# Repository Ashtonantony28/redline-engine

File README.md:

# Redline

A code-first digital twin of a 2.0 L naturally aspirated inline-4: parametric CAD (build123d),
crank-angle thermodynamics and combustion (Cantera), 1D gas dynamics, kinematics, dynamics and NVH,
structural FEA, and an engine control unit that runs hardware-in-the-loop on the Vortex-V RISC-V core.

All numbers are **modelled**. Plan: see `docs/PLAN.md`.

## Gallery

*The three.js replay (`viz/replay/index.html`) at 3000 rpm, wide-open throttle. It shows the CAD crank train moving with exact slider-crank kinematics, next to cylinder 1's P-V loop, the four cylinder pressures, crank torque and valve lift. Pressures come from the M4 1D gas-dynamics engine. **All numbers are modelled**; there is no physical engine. Recorded headless with `node viz/record_demo.mjs`. [MP4](docs/media/replay.mp4)*

| | |
|---|---|
|  |  |
|  |  |

*CAD renders from `cad/` (build123d). The interference audit is in [docs/CAD-AUDIT.md](docs/CAD-AUDIT.md).*

## Quick start
```
pip install -r requirements.txt
pytest -q
```

## Vehicle, replay and report (M10)
```
python -m vehicle.wltp                 # WLTP Class 3b L/100 km and g CO2/km (generic compact sedan, spec/vehicle.yaml)
python -m vehicle.accel                # 0-100 km/h and 80-120 km/h in gear
python -m vehicle.wot_fixture          # regenerate fixtures/wot/wot_coarse.csv from the M4 model (reviewed change)
python -m dyn.report --pressure m4     # M5 dynamics on real M4 / thermo pressure traces, vs the placeholder
python -m viz.build --check            # three.js replay viz/replay/index.html + headless check (node playwright)
python -m report.build                 # docs/REPORT.md technical report, figures under out/
pytest -q tests/test_m10_vehicle.py tests/test_m5_dynamics.py
```
The technical report is `docs/REPORT.md`; every number in it is computed by `report/build.py` and is modelled.

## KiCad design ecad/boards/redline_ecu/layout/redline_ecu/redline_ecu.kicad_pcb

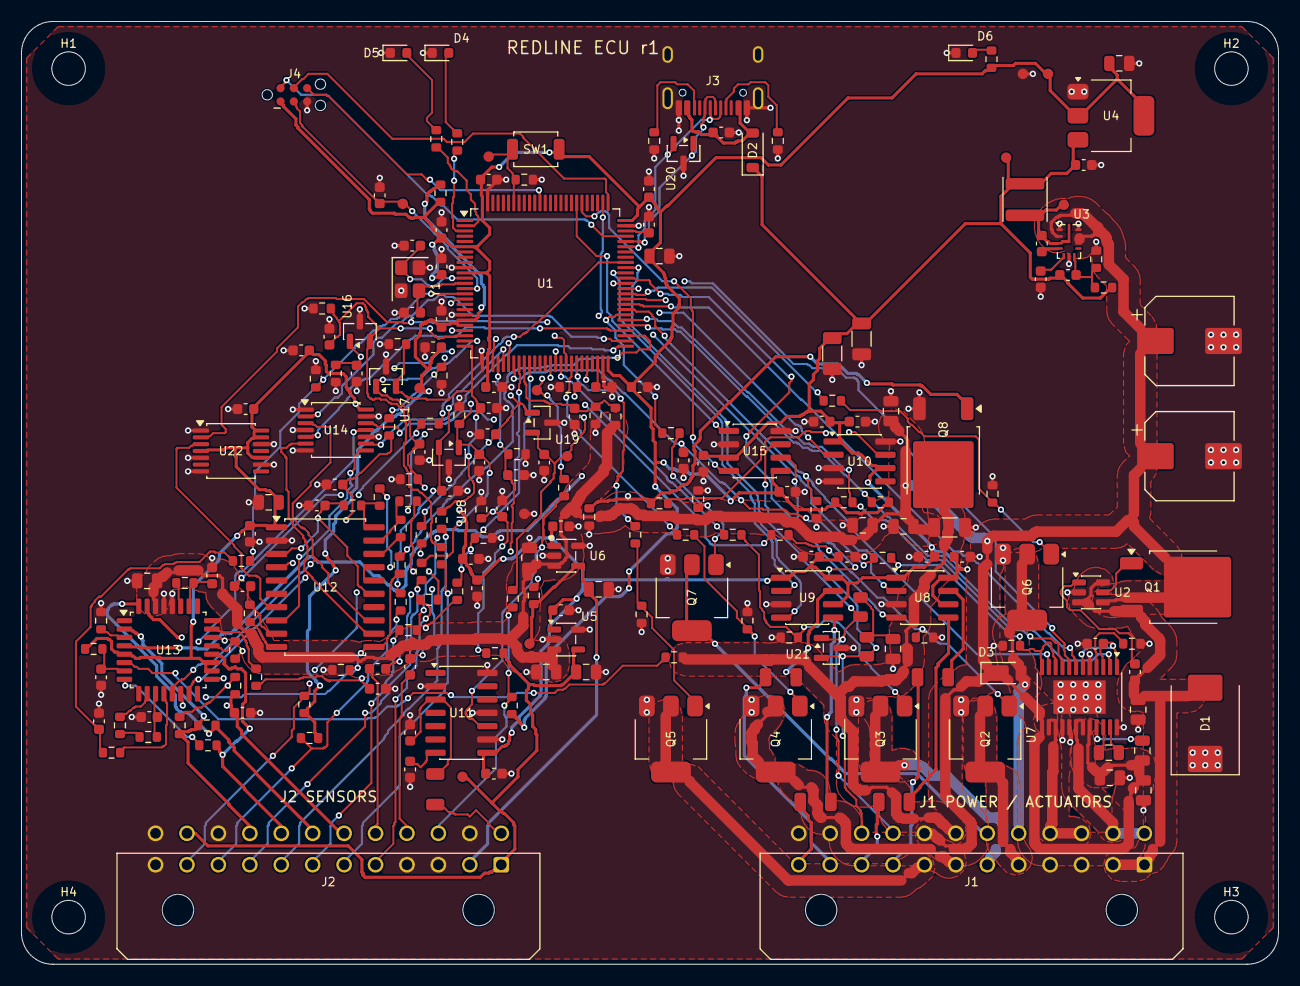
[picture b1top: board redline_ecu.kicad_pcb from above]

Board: 4 copper layers, 120.0 x 90.0 mm, 230 parts (0 on the bottom side), 158 nets.

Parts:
C1, C2: 47uF 50V; CP_Elec_8x10
C3: 4.7nF 100V X7R; C_0805_2012Metric
C4, C5, C6, C13, C14, C21, C28, C30, C31, C32, C35, C39, C40, C41, C42, C43, C44, C45, C48, C50, C53, C58, C61, C64, C68, C72, C73, C81, C83: 100nF 50V X7R; C_0603_1608Metric
C7: 47nF 100V X7R; C_0805_2012Metric
C8, C27, C38, C47, C49, C59, C69: 1uF 25V X7R; C_0603_1608Metric
C9, C74, C75, C76, C77, C78, C79, C80: 10nF 50V X7R; C_0603_1608Metric
C10, C12: 1uF 50V X7R; C_0805_2012Metric
C11, C54, C55, C62, C65, C67, C70: 100nF 100V X7R; C_0805_2012Metric
C15, C71, C82: 1nF 50V C0G; C_0603_1608Metric
C16, C19, C20: 33nF 50V X7R; C_0603_1608Metric
C17: 33nF 100V X7R; C_0805_2012Metric
C18: 220pF 50V C0G; C_0603_1608Metric
C22, C23: 3.3nF 50V C0G; C_0603_1608Metric
C24: 470pF 50V C0G; C_0603_1608Metric
C25: 2.2nF 50V C0G; C_0603_1608Metric
C26: 22nF 50V X7R; C_0603_1608Metric
C29, C63, C66: 4.7uF 16V X7R; C_0805_2012Metric
C33, C34: 12pF 50V C0G; C_0603_1608Metric
C36, C37: 2.2uF 10V X7R; C_0603_1608Metric
C46, C60: 10uF 16V X7R; C_0805_2012Metric
C51, C52: 22uF 16V X7R; C_1206_3216Metric
C56: 4.7uF 50V X7R; C_1206_3216Metric
C57: 20pF 50V C0G; C_0603_1608Metric
D1: 24V TVS Diode; D_SMC
D2: B5819W; D_SOD-123
D3: SBR3U60P1; D_PowerDI-123
D4: LED RED; LED_0603_1608Metric
D5: LED BLUE; LED_0603_1608Metric
D6: LED GREEN; LED_0603_1608Metric
FB1: 600 1A 100MHz; R_0603_1608Metric
H1, H2, H3, H4: MountingHole; MountingHole_3.2mm_M3
J1, J2: 43045-2400; Molex_Micro-Fit_3.0_43045-2400_2x12_P3.00mm_Horizontal
J3: TYPE-C-31-M-12; USB_C_Receptacle_HRO_TYPE-C-31-M-12
J4: TC2030-IDC-NL; Tag-Connect_TC2030-IDC-NL_2x03_P1.27mm_Vertical
L1: 3.3uH; L_Sunlord_SWPA4030S
Q1, Q8: DMTH6016LK3Q-13; TO-252-2
Q2, Q3, Q4, Q5, Q6, Q7: ZXMS6006DGQTA; SOT-223-3_TabPin2
R1, R2: 60.4 1%; R_0805_2012Metric
R3, R4: 5.1k 1%; R_0603_1608Metric
R5, R8, R12, R15, R17, R20, R26, R29, R34, R40, R62, R86: 10k 1%; R_0603_1608Metric
R6: 390 1%; R_0603_1608Metric
R7, R19, R25, R32, R38, R41, R42, R47, R49, R51, R53, R55, R57, R61, R64, R66, R68: 1k 1%; R_0603_1608Metric
R9, R13, R23, R39, R48, R50, R52, R54, R56, R58, R60: 100k 1%; R_0603_1608Metric
R10: 68k 1%; R_0603_1608Metric
R11, R21, R27: 6.8k 1%; R_0603_1608Metric
R14: 21.5k 1%; R_0603_1608Metric
R16: 301 1%; R_0603_1608Metric
R18: 61.9 0.1%; R_0603_1608Metric
R22: 470k 1%; R_0603_1608Metric
R24, R65: 4.7k 1%; R_0603_1608Metric
R28: 22 1%; R_0603_1608Metric
R30, R35, R36, R37, R63: 47k 1%; R_0603_1608Metric
R31: 1M 1%; R_0603_1608Metric
R33, R70, R72, R74, R76, R78, R80, R82, R84: 20k 1%; R_0603_1608Metric
R43, R44, R45, R46: 100 1%; R_1206_3216Metric
R59: 24.9k 1%; R_0603_1608Metric
R67, R69: 2.49k 1%; R_0603_1608Metric
R71, R73, R75, R77, R79, R81, R83: 13.3k 1%; R_0603_1608Metric
R85: 22k 1%; R_1206_3216Metric
SW1: TS-1088-AR02016; SW_SPST_TS-1088-xR020
TP1, TP2, TP3, TP4, TP5, TP6, TP7, TP8, TP9, TP10, TP11, TP12, TP13: TestPoint_Small; TestPoint_Pad_D1.0mm
U1: STM32H743VIT6; LQFP-100_14x14mm_P0.5mm
U2: LM74700QDBVRQ1; SOT-23-6
U3: LMR36015FSCQRNXRQ1; Texas_RNX0012C_VQFN-14-11-1EP_2x3mm_P0.5mm_EP0.25x1.825mm
U4: LDL1117S33R; SOT-223-3_TabPin2
U5, U6: TPS7B4250QDBVRQ1; SOT-23-5
U7: DRV8873HQPWPRQ1; HTSSOP-24-1EP_4.4x7.8mm_P0.65mm_EP3.2x5mm
U8, U9, U10: UCC27524AQDRQ1; SOIC-8_3.9x4.9mm_P1.27mm
U11: LM1815M/NOPB; SOIC-14_3.9x8.7mm_P1.27mm
U12: TPIC8101DWRQ1; SOIC-20W_7.5x12.8mm_P1.27mm
U13: CJ125; LQFP-32_7x7mm_P0.8mm
U14, U22: SN74AHCT125QPWRQ1; TSSOP-14_4.4x5mm_P0.65mm
U15: TCAN1044AVDRQ1; SOIC-8_3.9x4.9mm_P1.27mm
U16, U17, U18, U19, U20: TPD2E2U06QDBZRQ1; SOT-23
U21: ESD2CAN24DBZRQ1; SOT-23
Y1: 8MHz; Crystal_SMD_3225-4Pin_3.2x2.5mm

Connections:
3V3: C5.1, C40.1, C41.1, C42.1, C43.1, C44.1, C45.1, C46.1, C60.1, FB1.1, J4.1, R5.2, R8.2, R61.1, R65.2, SW1.1, TP3.1, U1.6, U1.11, U1.27, U1.50, U1.75, U1.100, U4.2, U15.5
5V: C4.1, C20.1, C21.1, C27.1, C28.1, C29.1, C30.1, C31.1, C32.1, C47.1, C48.1, C49.1, C50.1, C51.1, C52.1, C57.1, C59.1, C61.1, C64.1, C81.1, D2.1, L1.2, R17.2, R60.1, TP2.1, U4.3, U5.1, U6.1, U8.1, U8.6, U8.8, U9.1, U9.6, U9.8, U10.1, U10.6, U11.8, U12.1, U13.5, U13.18, U13.19, U14.14, U15.3, U22.4, U22.10, U22.13, U22.14
5V_S1: C63.1, J2.1, J2.23, R77.1, TP5.1, U5.4
5V_S2: C66.1, J2.2, R79.1, TP6.1, U6.4
BOOT0: R40.1, SW1.2, TP12.1, U1.94
CAM: C71.1, R64.2, TP10.1, U1.46, U19.2
CAM_IN: J2.15, R64.1, R65.1
CAN_H: J1.21, R1.1, U15.7, U21.1
CAN_L: J1.22, R2.2, U15.6, U21.2
CAN_RX: U1.81, U15.4
CAN_TX: U1.82, U15.1
CLT: J2.11, R66.1, R67.1
CLT_ADC: C72.1, R66.2, U1.31, U19.1
COM.CAN_SPLIT: C3.1, R1.2, R2.1
COM.USB_CC1: J3.A5, R3.1
COM.USB_CC2: J3.B5, R4.1
CRANK: R84.1, R86.2, TP9.1, U1.77
CRANK_P: J2.13, R85.1
ETB.CPH: C7.1, U7.22
ETB.CPL: C7.2, U7.23
ETB.DVDD: C8.1, U7.1, U7.3, U7.6
ETB.IPROPI: R6.1, R7.1, U7.10, U7.12
ETB.SR: R10.1, U7.4
ETB.VCP: C10.1, U7.21
ETB_DISABLE: R5.1, U1.56, U7.9
ETB_IN1: U1.59, U7.7
ETB_IN2: U1.60, U7.8
ETB_ISENSE: C9.1, R7.2, U1.32
ETB_M_N: J1.15, J1.16, U7.14, U7.15
ETB_M_P: J1.13, J1.14, U7.18, U7.19
ETB_NFAULT: R8.1, U1.55, U7.2
ETB_NSLEEP: R9.1, U1.58, U7.11
GND: C1.2, C2.2, C3.2, C4.2, C5.2, C6.2, C8.2, C9.2, C11.2, C12.2, C13.2, C14.2, C15.2, C16.2, C17.2, C18.2, C19.2, C20.2, C21.2, C25.2, C26.2, C27.2, C28.2, C29.2, C30.2, C31.2, C32.2, C33.2, C34.2, C35.2, C36.2, C37.2, C38.2, C39.2, C40.2, C41.2, C42.2, C43.2, C44.2, C45.2, C46.2, C47.2, C48.2, C49.2, C50.2, C51.2, C52.2, C54.2, C55.2, C56.2, C59.2, C60.2, C61.2, C62.2, C63.2, C64.2, C65.2, C66.2, C67.2, C68.2, C69.2, C70.2, C71.2, C72.2, C73.2, C74.2, C75.2, C76.2, C77.2, C78.2, C79.2, C80.2, C81.2, C82.2, C83.2, D1.1, D4.1, D5.1, D6.1, J1.3, J1.4, J1.23, J1.24, J2.3, J2.4, J2.12, J2.14, J2.22, J2.24, J3.A1, J3.A12, J3.B1, J3.B12, J3.SH, J4.5, Q2.3, Q3.3, Q4.3, Q5.3, Q6.3, Q7.3, Q8.3, R3.2, R4.2, R6.2, R9.2, R10.2, R12.2, R20.2, R26.2, R29.2, R33.2, R39.2, R40.2, R48.2, R50.2, R52.2, R54.2, R56.2, R58.2, R59.2, R62.2, R70.2, R72.2, R74.2, R76.2, R78.2, R80.2, R82.2, R84.2, TP7.1, TP8.1, U1.10, U1.19, U1.26, U1.49, U1.74, U1.99, U2.2, U3.1, U3.6, U3.11, U4.1, U5.2, U5.5, U6.2, U6.5, U7.5, U7.16, U7.17, U7.24, U7.25, U8.3, U9.3, U10.3, U10.4, U10.8, U11.2, U11.9, U11.11, U11.14, U12.2, U13.28, U13.29, U14.1, U14.4, U14.7, U14.10, U14.13, U15.2, U15.8, U16.3, U17.3, U18.3, U19.3, U20.3, U21.3, U22.1, U22.5, U22.7, U22.9, U22.12, Y1.2, Y1.4
HTR_CMD: U1.62, U10.2
IAT: J2.10, R68.1, R69.1
IAT_ADC: C73.1, R68.2, U1.30, U18.2
IGN1: J1.9, R43.2
IGN1_CMD: U1.63, U8.2
IGN2: J1.10, R44.2
IGN2_CMD: U1.64, U8.4
IGN3: J1.11, R45.2
IGN3_CMD: U1.65, U9.2
IGN4: J1.12, R46.2
IGN4_CMD: U1.66, U9.4
INJ1: J1.5, Q2.2
INJ1_CMD: R47.1, U1.39
INJ2: J1.6, Q3.2
INJ2_CMD: R49.1, U1.41
INJ3: J1.7, Q4.2
INJ3_CMD: R51.1, U1.43
INJ4: J1.8, Q5.2
INJ4_CMD: R53.1, U1.44
KL.CH1FB: R37.2, U12.18
KL.CH1N: R35.2, R37.1, U12.19
KL.CH1P: R30.1, R36.2, U12.20
KL.CH2N: U12.16, U12.17
KL.CJ_CF: C13.1, R13.2, U13.26
KL.CJ_CM: C14.1, R15.2, U13.11
KL.CJ_DIAHD: R11.1, U13.6
KL.CJ_OSZ: R12.1, U13.3
KL.CJ_RF: R13.1, U13.27
KL.CJ_RM: R14.1, U13.10
KL.CJ_RM2: R14.2, R15.1
KL.CJ_RS: R16.1, U13.8
KL.CJ_RST: C15.1, R17.1, U13.7
KL.CJ_UA: R19.1, U13.23
KL.CJ_UA_F: C16.1, R19.2, R21.1
KL.CJ_UP: R22.1, R23.1, R24.1, U13.22
KL.CJ_UR: R25.1, U13.12
KL.CJ_UR_F: C19.1, R25.2, R27.1
KL.CJ_US: R24.2, U13.21
KL.HTR_DRV: R28.1, U10.7
KL.HTR_GATE: Q8.1, R28.2, R29.1, U13.4
KL.INTHOLD_5V: U12.7, U22.3
KL.KNK_AN: C22.2, R36.1
KL.KNK_AP: C23.2, R35.1
KL.KNK_CK: C24.1, R32.2
KL.KNK_CS_5V: U12.8, U14.8
KL.KNK_OUT: C25.1, R34.1, U12.4
KL.KNK_VREF: C26.1, R30.2, U12.3, U12.15
KL.KNK_XIN: C24.2, R31.1, U12.9
KL.KNK_XOUT: R31.2, U12.10
KL.LAM_CS_5V: U13.17, U14.11
KL.MISO_5V: R38.1, R39.1, U12.11, U13.14
KL.MOSI_5V: U12.12, U13.15, U14.6
KL.SCLK_5V: U12.13, U13.13, U14.3
KNK_CLK: R32.1, U1.67
KNK_CS: U1.51, U14.9
KNK_INTHOLD: U1.42, U22.2
KNOCK_ADC: R33.1, R34.2, U1.16
KNOCK_N: C22.1, J2.17
KNOCK_P: C23.1, J2.16
LAMBDA_UA: R20.1, R21.2, U1.35
LAMBDA_UR: R26.1, R27.2, U1.15
LAM_CS: U1.40, U14.12
LSU_HTR_N: J1.19, Q8.2, R11.2
LSU_IA: J2.21, R18.1, R22.2, U13.2
LSU_IP: J2.19, R18.2, U13.32
LSU_UN: C18.1, J2.18, R23.2, U13.31
LSU_VM: J2.20, R16.2, U13.20
MAP: J2.9, R71.1
MAP_ADC: C74.1, R70.1, R71.2, U1.28, U18.1
MCU.HSE_IN: C33.1, U1.12, Y1.1
MCU.HSE_OUT: C34.1, U1.13, Y1.3
MCU.LED_FAULT: R41.1, U1.3
MCU.LED_FAULT_A: D4.2, R41.2
MCU.LED_STATUS: R42.1, U1.2
MCU.LED_STATUS_A: D5.2, R42.2
MCU.VCAP_1: C36.1, U1.48
MCU.VCAP_2: C37.1, U1.73
NRST: C35.1, J4.3, TP11.1, U1.14
OUT.IGN1_DRV: R43.1, U8.7
OUT.IGN2_DRV: R44.1, U8.5
OUT.IGN3_DRV: R45.1, U9.7
OUT.IGN4_DRV: R46.1, U9.5
OUT.INJ1_IN: Q2.1, R47.2, R48.1
OUT.INJ2_IN: Q3.1, R49.2, R50.1
OUT.INJ3_IN: Q4.1, R51.2, R52.1
OUT.INJ4_IN: Q5.1, R53.2, R54.1
OUT.PUMP_IN: Q7.1, R55.2, R56.1
OUT.VVT_IN: Q6.1, R57.2, R58.1
PPS1: J2.7, R73.1
PPS1_ADC: C75.1, R72.1, R73.2, U1.24, U17.1
PPS2: J2.8, R75.1
PPS2_ADC: C76.1, R74.1, R75.2, U1.25, U17.2
PUMP: J1.18, Q7.2
PUMP_CMD: R55.1, U1.57
PWR.BUCK_BOOT: C53.1, U3.4
PWR.BUCK_FB: C57.2, R59.1, R60.2, U3.7
PWR.BUCK_SW: C53.2, L1.1, TP13.1, U3.3, U3.12
PWR.BUCK_VCC: C69.1, U3.5
PWR.PWR_LED_A: D6.2, R61.2
PWR.RB_GATE: Q1.1, U2.5
PWR.RB_VCAP: C58.1, U2.1
S5V1_MON: C77.1, R76.1, R77.2, U1.33
S5V2_MON: C78.1, R78.1, R79.2, U1.29
SENS.VR_IN: C82.1, R85.2, U11.3
SENS.VR_OUT: R86.1, U11.10
SENS.VR_PEAK: C83.1, U11.7
SPI2_MISO: R38.2, U1.53
SPI2_MOSI: U1.54, U14.5
SPI2_SCK: U1.52, U14.2
SWCLK: J4.4, U1.76
SWDIO: J4.2, U1.72
SWO: J4.6, U1.89
TPS1: J2.5, R81.1
TPS1_ADC: C79.1, R80.1, R81.2, U1.22, U16.1
TPS2: J2.6, R83.1
TPS2_ADC: C80.1, R82.1, R83.2, U1.23, U16.2
USB_N: J3.A7, J3.B7, U1.70, U20.2
USB_P: J3.A6, J3.B6, U1.71, U20.1
VBAT: C1.1, C2.1, C10.2, C11.1, C12.1, C17.1, C54.1, C55.1, C56.1, C62.1, C65.1, C67.1, D3.1, J1.20, Q1.2, R63.1, TP1.1, U2.4, U3.2, U3.9, U3.10, U5.3, U6.3, U7.13, U7.20, U13.30
VBAT_IN: C58.2, C70.1, D1.2, J1.1, J1.2, Q1.3, U2.3, U2.6
VBAT_SENSE: C68.1, R62.1, R63.2, U1.34
VBUS: C6.1, D2.2, J3.A4, J3.A9, J3.B4, J3.B9
VDDA: C38.1, C39.1, FB1.2, R67.2, R69.2, TP4.1, U1.20, U1.21
VVT: D3.2, J1.17, Q6.2
VVT_CMD: R57.1, U1.61

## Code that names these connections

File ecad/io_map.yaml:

# Redline ECU board: firmware I/O -> MCU pin -> net -> harness pin.
#
# `firmware` entries are the I/O the portable core (ecu/include/ecu/*.h, ADR 0003) consumes or
# produces; check_design.py parses the headers and fails if any of them is missing here.
# `board` entries are hardware the firmware does not use yet (plan section 3.7 lists VVT control,
# and the board brief adds the second pedal track, fuel pump relay, CAN, USB and SWD).
#
#   source   the header symbol (struct field, entry point, event type) this entry serves
#   mcu      {pin: net} on U1
#   harness  {connector.pin: net}
#   chain    nets from the MCU to the harness; each consecutive pair must share a component
#            (the conditioning or driver stage), proven on the netlist

timebase:
  source: ECU_TIMER_HZ (1 MHz, 32-bit wrap-safe ticks), hal_emit_event
  note: TIM2 is the 32-bit timer; crank (CH1) and cam (CH3) capture on it, so captured ticks and
        event ticks share one clock. TIM1 / TIM8 output compares are slaved to it in the HAL.
  mcu: {PA15: CRANK, PB10: CAM}

firmware:
  crank:
    source: ecu_crank_edge(e, tick)
    mcu: {PA15: CRANK}
    harness: {J2.13: CRANK_P, J2.14: GND}
    chain: [CRANK, SENS.VR_OUT, SENS.VR_IN, CRANK_P]
  cam:
    source: ecu_cam_edge(e, tick)
    mcu: {PB10: CAM}
    harness: {J2.15: CAM_IN}
    chain: [CAM, CAM_IN]
  knock:
    source: ecu_knock_window(e, cyl, counts)
    mcu: {PB12: KNK_CS, PB13: SPI2_SCK, PB14: SPI2_MISO, PB15: SPI2_MOSI, PE12: KNK_INTHOLD, PA8: KNK_CLK, PC1: KNOCK_ADC}
    harness: {J2.16: KNOCK_P, J2.17: KNOCK_N}
    chain: [KNK_INTHOLD, KL.INTHOLD_5V, KL.CH1N, KL.KNK_AP, KNOCK_P]
  map_pa:
    source: ecu_inputs_t.map_pa
    mcu: {PA4: MAP_ADC}
    harness: {J2.9: MAP}
    chain: [MAP_ADC, MAP]
  iat_k:
    source: ecu_inputs_t.iat_k
    mcu: {PA6: IAT_ADC}
    harness: {J2.10: IAT}
    chain: [IAT_ADC, IAT]
  clt_k:
    source: ecu_inputs_t.clt_k
    mcu: {PA7: CLT_ADC}
    harness: {J2.11: CLT}
    chain: [CLT_ADC, CLT]
  tps1_deg:
    source: ecu_inputs_t.tps1_deg
    mcu: {PA0: TPS1_ADC}
    harness: {J2.5: TPS1, J2.1: 5V_S1}
    chain: [TPS1_ADC, TPS1]
  tps2_deg:
    source: ecu_inputs_t.tps2_deg
    mcu: {PA1: TPS2_ADC}
    harness: {J2.6: TPS2, J2.2: 5V_S2}
    chain: [TPS2_ADC, TPS2]
  pedal:
    source: ecu_inputs_t.pedal
    mcu: {PA2: PPS1_ADC}
    harness: {J2.7: PPS1, J2.1: 5V_S1}
    chain: [PPS1_ADC, PPS1]
  lambda:
    source: ecu_inputs_t.lambda
    mcu: {PB1: LAMBDA_UA, PC0: LAMBDA_UR, PE10: LAM_CS}
    harness: {J2.18: LSU_UN, J2.19: LSU_IP, J2.20: LSU_VM, J2.21: LSU_IA}
    chain: [LAMBDA_UA, KL.CJ_UA_F, KL.CJ_UA]
  vbatt:
    source: ecu_inputs_t.vbatt
    mcu: {PB0: VBAT_SENSE}
    harness: {J1.1: VBAT_IN, J1.2: VBAT_IN}
    chain: [VBAT_SENSE, VBAT, VBAT_IN]
  etc_voltage:
    source: ecu_outputs_t.etc_voltage
    mcu: {PD12: ETB_IN1, PD13: ETB_IN2, PD11: ETB_NSLEEP, PD9: ETB_DISABLE, PD8: ETB_NFAULT, PC4: ETB_ISENSE}
    harness: {J1.13: ETB_M_P, J1.14: ETB_M_P, J1.15: ETB_M_N, J1.16: ETB_M_N}
    chain: [ETB_IN1, ETB_M_P]
  inj:
    source: ECU_EV_INJ x ECU_NCYL (cyl n -> INJ<n+1>)
    per_cylinder: true
    mcu: {PE9: INJ1_CMD, PE11: INJ2_CMD, PE13: INJ3_CMD, PE14: INJ4_CMD}
    harness: {J1.5: INJ1, J1.6: INJ2, J1.7: INJ3, J1.8: INJ4}
    chains:
      - [INJ1_CMD, OUT.INJ1_IN, INJ1]
      - [INJ2_CMD, OUT.INJ2_IN, INJ2]
      - [INJ3_CMD, OUT.INJ3_IN, INJ3]
      - [INJ4_CMD, OUT.INJ4_IN, INJ4]
  ign:
    source: ECU_EV_DWELL / ECU_EV_SPARK x ECU_NCYL (cyl n -> IGN<n+1>)
    per_cylinder: true
    mcu: {PC6: IGN1_CMD, PC7: IGN2_CMD, PC8: IGN3_CMD, PC9: IGN4_CMD}
    harness: {J1.9: IGN1, J1.10: IGN2, J1.11: IGN3, J1.12: IGN4}
    chains:
      - [IGN1_CMD, OUT.IGN1_DRV, IGN1]
      - [IGN2_CMD, OUT.IGN2_DRV, IGN2]
      - [IGN3_CMD, OUT.IGN3_DRV, IGN3]
      - [IGN4_CMD, OUT.IGN4_DRV, IGN4]

board:
  pedal2:
    note: second pedal track (plausibility; firmware reads one pedal today)
    mcu: {PA3: PPS2_ADC}
    harness: {J2.8: PPS2, J2.2: 5V_S2}
    chain: [PPS2_ADC, PPS2]
  sensor_supply_monitor:
    mcu: {PC5: S5V1_MON, PA5: S5V2_MON}
    harness: {J2.1: 5V_S1, J2.2: 5V_S2, J2.23: 5V_S1}
    chain: [S5V1_MON, 5V_S1]
  vvt:
    note: intake cam phaser valve (spec/engine.yaml vvt_intake_range_deg); no firmware loop yet
    mcu: {PD14: VVT_CMD}
    harness: {J1.17: VVT}
    chain: [VVT_CMD, OUT.VVT_IN, VVT]
  fuel_pump_relay:
    mcu: {PD10: PUMP_CMD}
    harness: {J1.18: PUMP}
    chain: [PUMP_CMD, OUT.PUMP_IN, PUMP]
  lsu_heater:
    mcu: {PD15: HTR_CMD}
    harness: {J1.19: LSU_HTR_N, J1.20: VBAT}
    chain: [HTR_CMD, KL.HTR_DRV, KL.HTR_GATE, LSU_HTR_N]
  can:
    mcu: {PD0: CAN_RX, PD1: CAN_TX}
    harness: {J1.21: CAN_H, J1.22: CAN_L}
    chain: [CAN_TX, CAN_H]
  usb_debug:
    mcu: {PA11: USB_N, PA12: USB_P}
    harness: {J3.A6: USB_P, J3.A7: USB_N}
    chain: [USB_P]
  swd:
    mcu: {PA13: SWDIO, PA14: SWCLK, PB3: SWO, NRST: NRST}
    harness: {J4.2: SWDIO, J4.4: SWCLK, J4.6: SWO, J4.3: NRST}
    chain: [SWDIO]

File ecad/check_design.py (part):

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    nets, comps = netlist()
    mcu = comps["U1"]
    for pin, net in entry.get("mcu", {}).items():
        assert mcu.pins.get(pin) == net, "%s: U1.%s is on %s, io_map says %s" % (name, pin, mcu.pins.get(pin), net)
    for loc, net in entry.get("harness", {}).items():
        ref, pad = loc.split(".")
        assert comps[ref].pads.get(pad) == net, "%s: %s pad %s is on %s, io_map says %s" % (
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

def test_mcu_pin_plan_complete():
    """Each MCU pin is a mapped function, a power pin, or an explicit no-connect; mapped pins are io_map pins."""
    nets, comps = netlist()
    mcu = comps["U1"]
    m = io_map()
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        elif pin in support:
            assert net == support[pin], (pin, net)
        else:
            assert nets[net]["kind"] == "NotConnected", "U1.%s is on %s but not in io_map.yaml" % (pin, net)
    assert len(mcu.pads) == 100


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    tvs = LIMITS["SMCJ24CA"]
    assert tvs["vrwm"] >= LOADS["vbat_jump"] and tvs["vbr_min"] > LOADS["vbat_jump"]
    _, comps = netlist()
    assert comps["D1"].attrs["mpn"] == "SMCJ24CA" and set(comps["D1"].pins.values()) == {"VBAT_IN", "GND"}
    checked = set()
    for net in ("VBAT", "VBAT_IN"):
        for c in _parts_on(net):
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

def test_limit_low_side_drivers():
    """Injector / VVT / relay currents within ZXMS6006DGQ ratings; flyback handled; harness pins reached."""
    zx = LIMITS["ZXMS6006DGQ"]
    mv = spec("mvem.yaml")
    vmax = LOADS["vbat_max_operating"]
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        assert not [c for c in _parts_on(net) if c.attrs.get("type") == "rectifier" or c.ref.startswith("D")], net
    # VVT: freewheel Schottky to VBAT sized for the solenoid current
    d3 = comps["D3"]
    assert d3.pins == {"A": "VVT", "K": "VBAT"}
    assert vmax / LOADS["vvt_r_min"] <= LIMITS["SBR3U60P1"]["if_max"]


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    dm = LIMITS["DMTH6016LK3Q"]
    assert LOADS["heater_i_max"] <= 0.5 * dm["id_ta25"]
    assert LOADS["heater_i_max"] ** 2 * dm["rds_4v5"] < 1.0  # W, conduction loss in the DPAK
    assert comps["Q8"].pins == {"G": "KL.HTR_GATE", "D": "LSU_HTR_N", "S": "GND"}


def test_limit_etb():
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        net = u12.pins[pin]
        drivers = [c for c in _parts_on(net) if str(c.attrs.get("mpn", "")).startswith("SN74AHCT125")]
        assert drivers, "TPIC8101 %s (%s) is not level shifted" % (pin, net)
    assert resistors_between("KL.MISO_5V", "SPI2_MISO")  # 5 V SDO into a 5 V-tolerant pin through 1k


def _walk(d, prefix=""):
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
